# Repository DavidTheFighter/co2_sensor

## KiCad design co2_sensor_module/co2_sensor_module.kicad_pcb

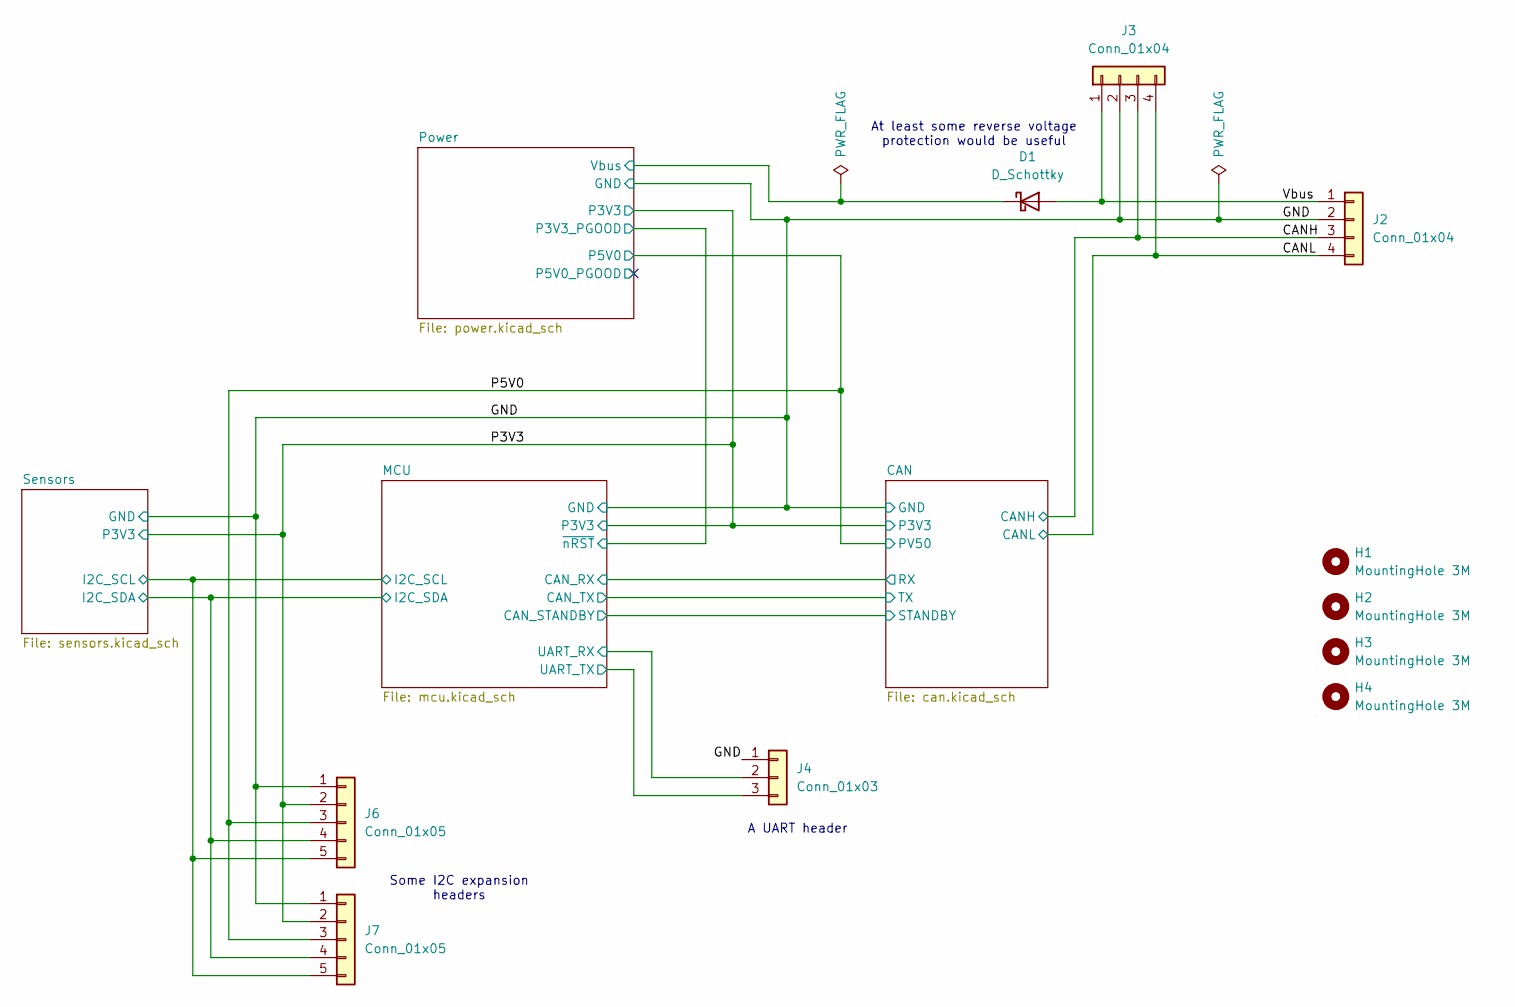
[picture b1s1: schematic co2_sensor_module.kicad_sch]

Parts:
D1: D_Schottky; D_SOD-123; LCSC C8598
H1, H2, H3, H4: MountingHole 3M; MountingHole_3.2mm_M3
J2, J3: Conn_01x04; JST_PH_B4B-PH-K_1x04_P2.00mm_Vertical
J4: Conn_01x03; PinHeader_1x03_P2.54mm_Vertical
J6, J7: Conn_01x05; PinHeader_1x05_P2.54mm_Vertical

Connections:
/CANH: J2.3, J3.3; also elsewhere on the board
/CANL: J2.4, J3.4; also elsewhere on the board
/GND: J2.2, J3.2, J4.1, J6.1, J7.1; also elsewhere on the board
/MCU/I2C_SCL: J6.5, J7.5; also elsewhere on the board
/MCU/I2C_SDA: J6.4, J7.4; also elsewhere on the board
/MCU/UART_RX: J4.2; also elsewhere on the board
/MCU/UART_TX: J4.3; also elsewhere on the board
/P3V3: J6.2, J7.2; also elsewhere on the board
/P5V0: J6.3, J7.3; also elsewhere on the board
/Power/Vbus: D1.1 (K); also elsewhere on the board
/Vbus: D1.2 (A), J2.1, J3.1

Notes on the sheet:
Some I2C expansion headers
At least some reverse voltage protection would be useful
A UART header

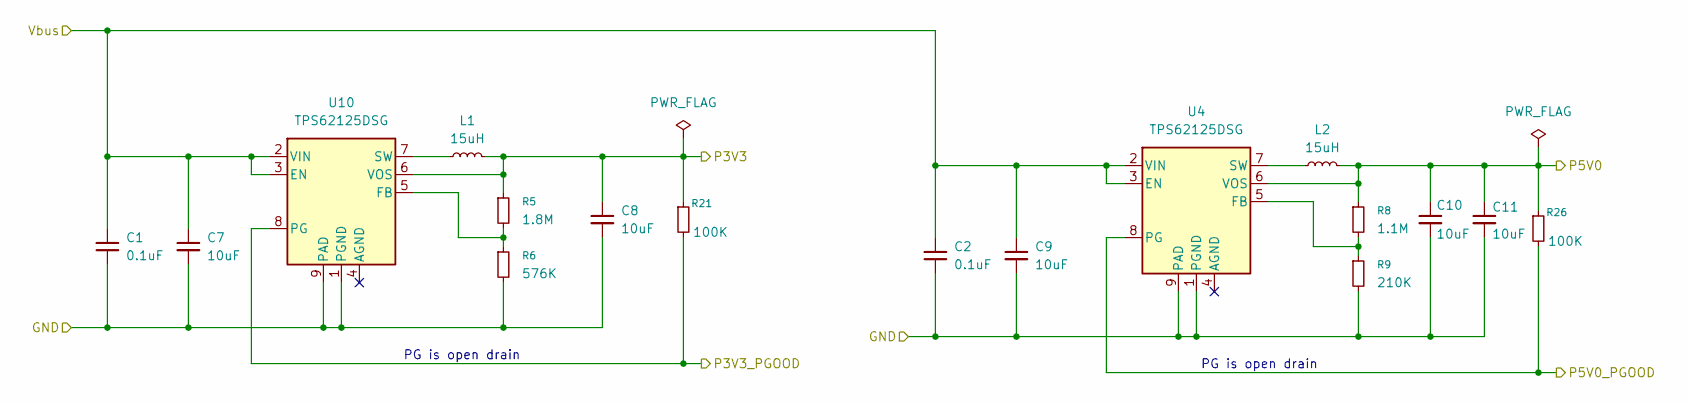
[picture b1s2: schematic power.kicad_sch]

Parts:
C1, C2: 0.1uF; C_0603_1608Metric; LCSC C14663
C7, C8, C9, C10, C11: 10uF; C_0805_2012Metric; LCSC C15850
L1, L2: 15uH; L_1008_2520Metric; LCSC C5832376
R5: 1.8M; R_0402_1005Metric; LCSC C2933079
R6: 576K; R_0402_1005Metric; LCSC C2085028
R8: 1.1M; R_0402_1005Metric; LCSC C2930013
R9: 210K; R_0402_1005Metric; LCSC C2998176
R21, R26: 100K; C_0402_1005Metric; LCSC C25741
U4, U10: TPS62125DSG; Texas_DSG0008A_WSON-8-1EP_2x2mm_P0.5mm_EP0.9x1.6mm; LCSC C324076

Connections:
/GND: C1.2, C2.2, C7.2, C8.2, C9.2, C10.2, C11.2, R6.2, R9.2, U4.1 (PGND), U4.9 (PAD), U10.1 (PGND), U10.9 (PAD); also elsewhere on the board
/MCU/~nRST: R21.2, U10.8 (PG); also elsewhere on the board
/P3V3: C8.1, L1.2, R5.1, R21.1, U10.6 (VOS); also elsewhere on the board
/P5V0: C10.1, C11.1, L2.2, R8.1, R26.1, U4.6 (VOS); also elsewhere on the board
/Power/P5V0_PGOOD: R26.2, U4.8 (PG)
/Power/Vbus: C1.1, C2.1, C7.1, C9.1, U4.2 (VIN), U4.3 (EN), U10.2 (VIN), U10.3 (EN); also elsewhere on the board
unnamed: R8.2, R9.1, U4.5 (FB)
unnamed: L2.1, U4.7 (SW)
unnamed: R5.2, R6.1, U10.5 (FB)
unnamed: L1.1, U10.7 (SW)

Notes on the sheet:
PG is open drain

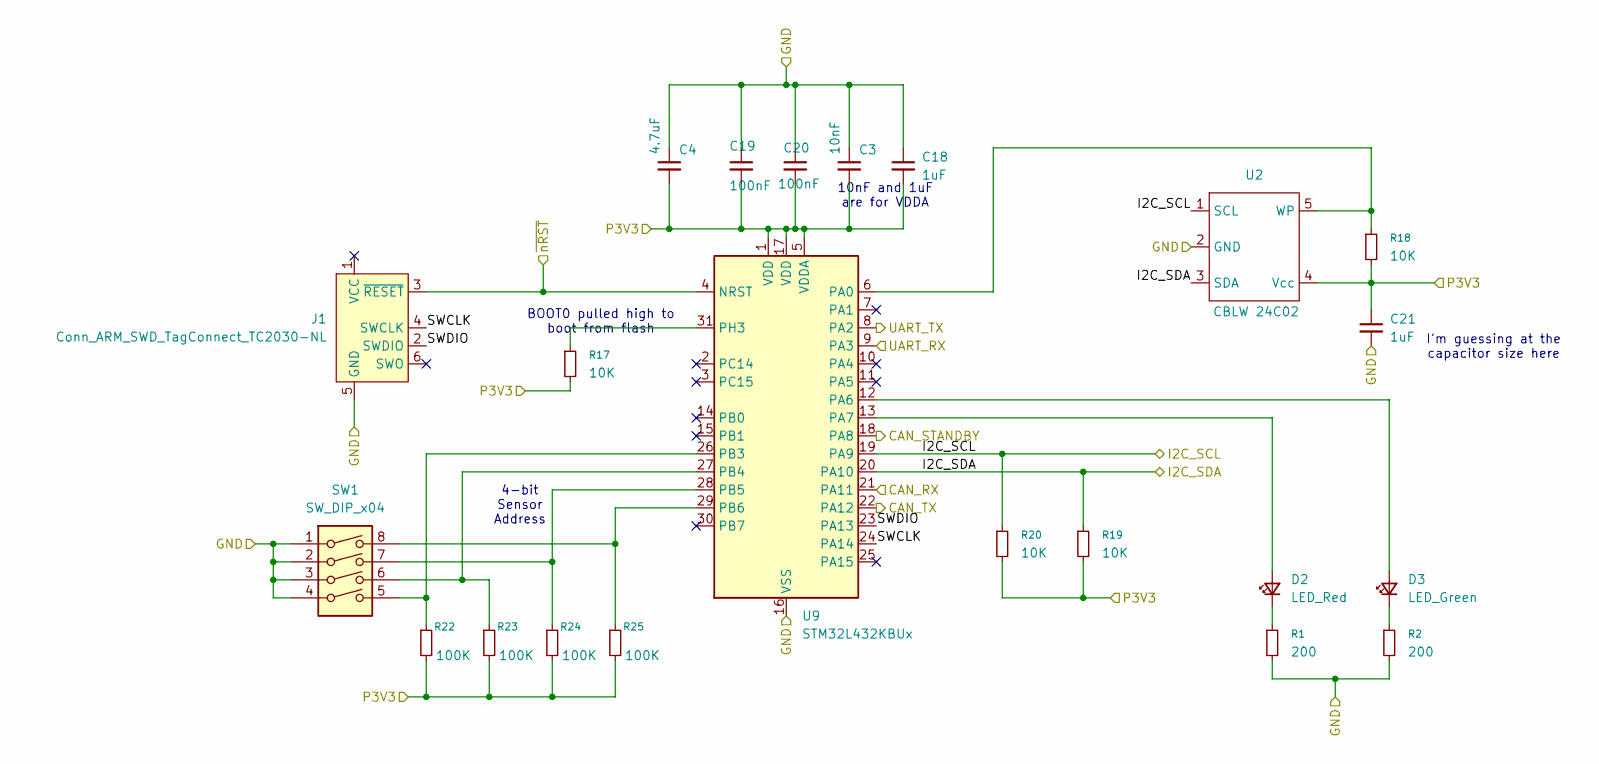
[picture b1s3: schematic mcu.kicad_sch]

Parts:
C3: 10nF; C_0402_1005Metric; LCSC C15195
C4: 4.7uF; C_0603_1608Metric; LCSC C19666
C18, C21: 1uF; C_0603_1608Metric; LCSC C15849
C19, C20: 100nF; C_0402_1005Metric; LCSC C1525
D2: LED_Red; LED_0805_2012Metric; LCSC C84256
D3: LED_Green; LED_0805_2012Metric; LCSC C2297
J1: Conn_ARM_SWD_TagConnect_TC2030-NL; Tag-Connect_TC2030-IDC-NL_2x03_P1.27mm_Vertical
R1, R2: 200; R_0603_1608Metric; LCSC C8218
R17, R18, R19, R20: 10K; R_0402_1005Metric; LCSC C25744
R22, R23, R24, R25: 100K; C_0402_1005Metric; LCSC C25741
SW1: SW_DIP_x04; SW_DIP_SPSTx04_Slide_9.78x12.34mm_W7.62mm_P2.54mm
U2: CBLW 24C02; SOT-23-5; LCSC C18723540
U9: STM32L432KBUx; QFN-32-1EP_5x5mm_P0.5mm_EP3.45x3.45mm; LCSC C2928224

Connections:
/CAN/RX: U9.21 (PA11); also elsewhere on the board
/CAN/STANDBY: U9.18 (PA8); also elsewhere on the board
/CAN/TX: U9.22 (PA12); also elsewhere on the board
/GND: C3.1, C4.1, C18.1, C19.1, C20.1, C21.2, J1.5 (GND), R1.2, R2.2, SW1.1, SW1.2, SW1.3, SW1.4, U2.2 (GND), U9.16 (VSS), U9.32 (VSS), U9.33 (VSS); also elsewhere on the board
/MCU/I2C_SCL: R20.1, U2.1 (SCL), U9.19 (PA9); also elsewhere on the board
/MCU/I2C_SDA: R19.1, U2.3 (SDA), U9.20 (PA10); also elsewhere on the board
/MCU/SWCLK: J1.4 (SWCLK), U9.24 (PA14)
/MCU/SWDIO: J1.2 (SWDIO), U9.23 (PA13)
/MCU/UART_RX: U9.9 (PA3); also elsewhere on the board
/MCU/UART_TX: U9.8 (PA2); also elsewhere on the board
/MCU/~nRST: J1.3 (~RESET), U9.4 (NRST); also elsewhere on the board
/P3V3: C3.2, C4.2, C18.2, C19.2, C20.2, C21.1, R17.2, R18.2, R19.2, R20.2, R22.2, R23.2, R24.2, R25.2, U2.4 (Vcc), U9.1 (VDD), U9.5 (VDDA), U9.17 (VDD); also elsewhere on the board
unnamed: D2.2 (A), U9.13 (PA7)
unnamed: D2.1 (K), R1.1
unnamed: D3.2 (A), U9.12 (PA6)
unnamed: D3.1 (K), R2.1
unnamed: R18.1, U2.5 (WP), U9.6 (PA0)
unnamed: R22.1, SW1.5, U9.26 (PB3)
unnamed: R23.1, SW1.6, U9.27 (PB4)
unnamed: R24.1, SW1.7, U9.28 (PB5)
unnamed: R25.1, SW1.8, U9.29 (PB6)
unnamed: R17.1, U9.31 (PH3)

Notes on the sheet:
BOOT0 pulled high to boot from flash
I'm guessing at the capacitor size here
10nF and 1uF are for VDDA
4-bit Sensor Address

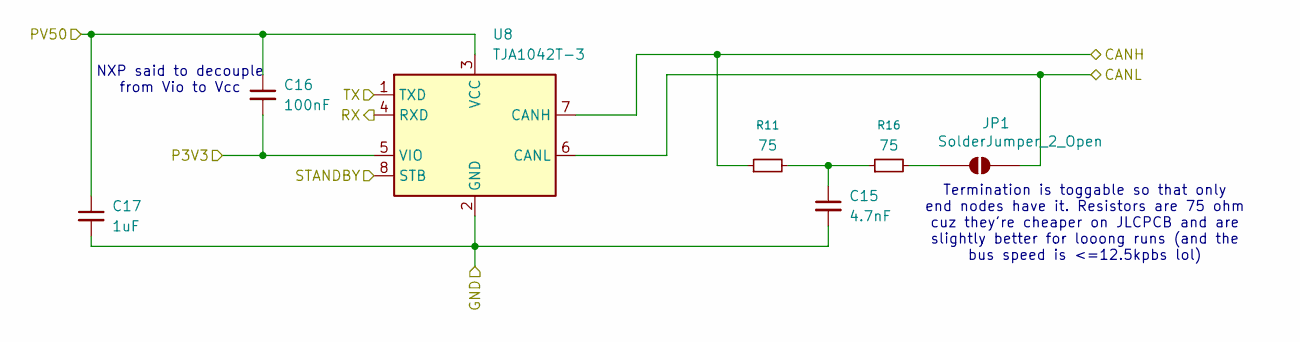
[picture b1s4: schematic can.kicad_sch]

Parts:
C15: 4.7nF; C_0805_2012Metric; LCSC C1744
C16: 100nF; C_0402_1005Metric; LCSC C1525
C17: 1uF; C_0603_1608Metric; LCSC C15849
JP1: SolderJumper_2_Open; SolderJumper-2_P1.3mm_Open_TrianglePad1.0x1.5mm
R11, R16: 75; R_0603_1608Metric; LCSC C4275
U8: TJA1042T-3; SOIC-8_3.9x4.9mm_P1.27mm; LCSC C132227

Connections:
/CAN/RX: U8.4 (RXD); also elsewhere on the board
/CAN/STANDBY: U8.8 (STB); also elsewhere on the board
/CAN/TX: U8.1 (TXD); also elsewhere on the board
/CANH: R11.1, U8.7 (CANH); also elsewhere on the board
/CANL: JP1.2 (B), U8.6 (CANL); also elsewhere on the board
/GND: C15.2, C17.2, U8.2 (GND); also elsewhere on the board
/P3V3: C16.2, U8.5 (VIO); also elsewhere on the board
/P5V0: C16.1, C17.1, U8.3 (VCC); also elsewhere on the board
unnamed: C15.1, R11.2, R16.1
unnamed: JP1.1 (A), R16.2

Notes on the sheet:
Termination is toggable so that only end nodes have it. Resistors are 75 ohm cuz they're cheaper on JLCPCB and are slightly better for looong runs (and the bus speed is <=12.5kpbs lol)
NXP said to decouple from Vio to Vcc

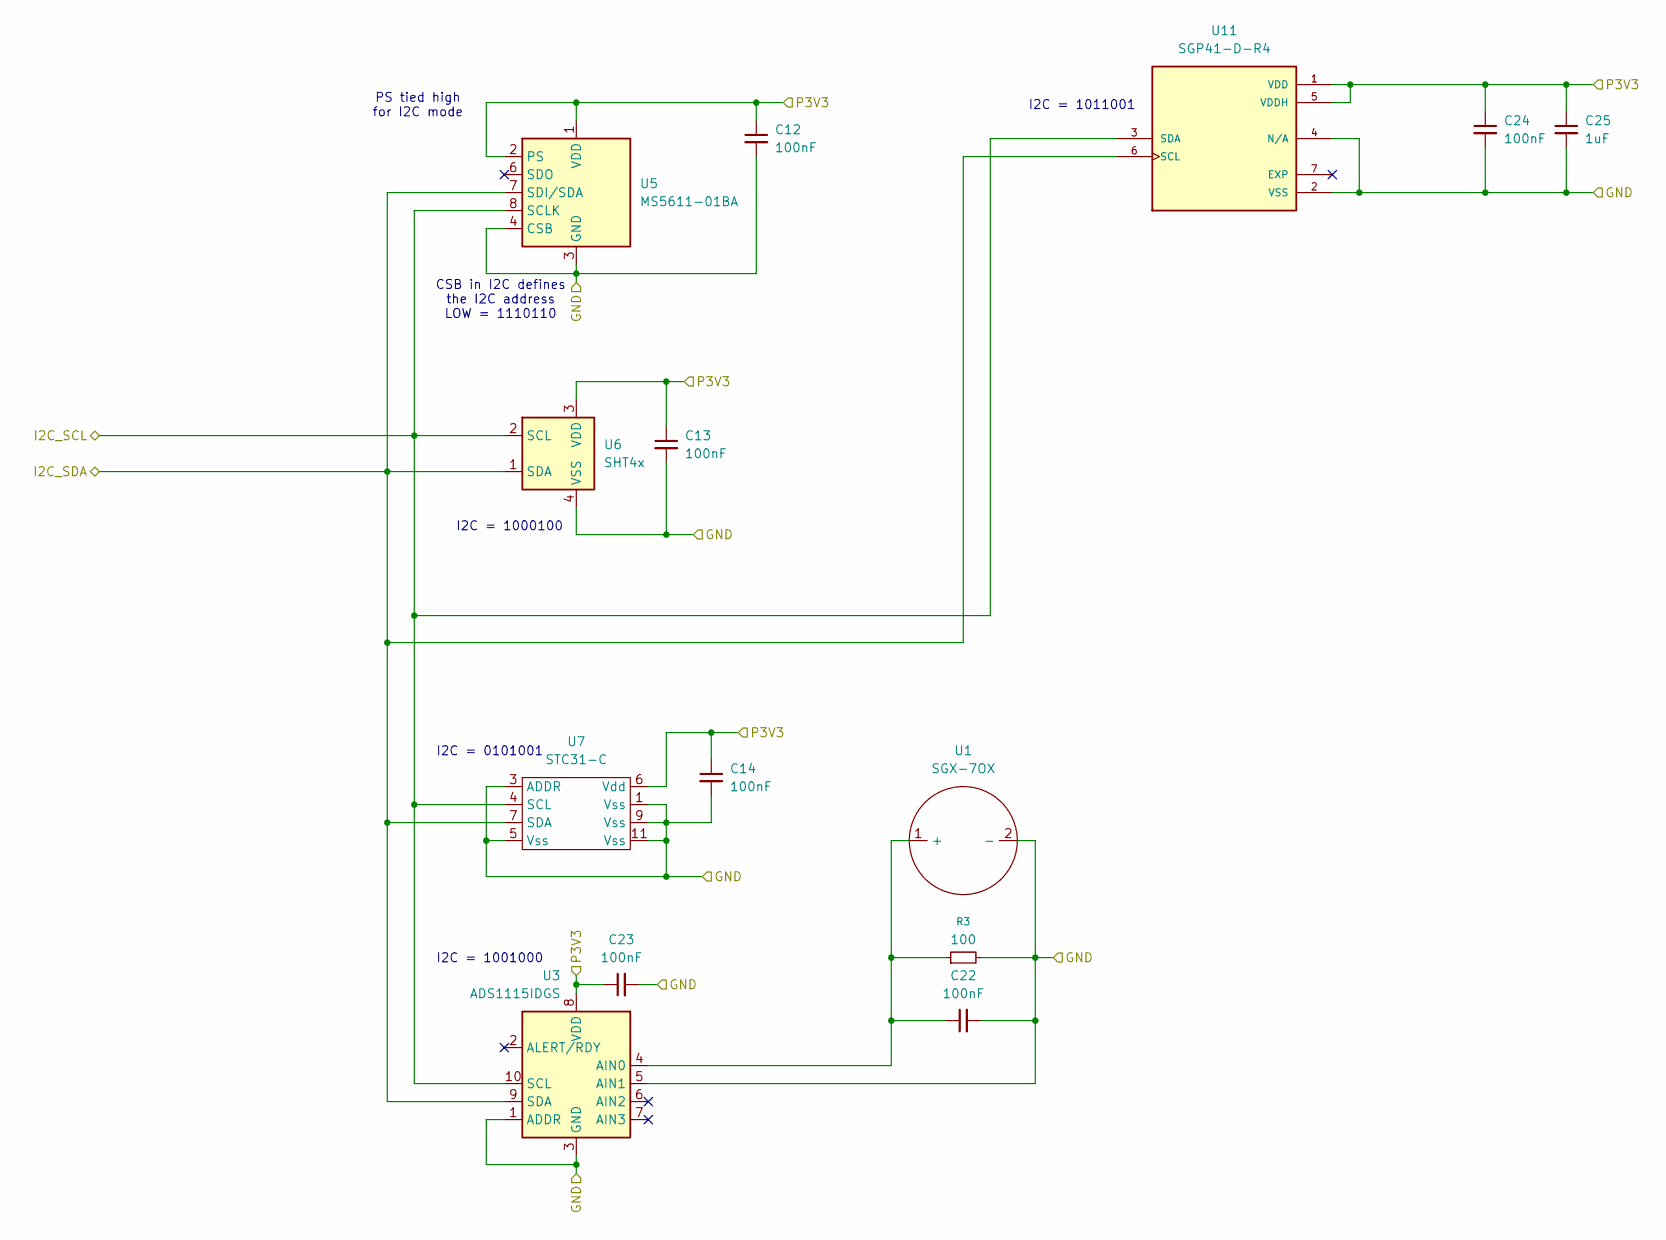
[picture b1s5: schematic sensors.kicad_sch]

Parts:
C12, C13, C14, C22, C23, C24: 100nF; C_0402_1005Metric; LCSC C1525
C25: 1uF; C_0603_1608Metric; LCSC C15849
R3: 100; R_0603_1608Metric; LCSC C122970
U1: SGX-7OX
U3: ADS1115IDGS; TSSOP-10_3x3mm_P0.5mm; LCSC C37593
U5: MS5611-01BA; LGA-8_3x5mm_P1.25mm; LCSC C15639
U6: SHT4x; Sensirion_DFN-4_1.5x1.5mm_P0.8mm_SHT4x_NoCentralPad; LCSC C2909890
U7: STC31-C; STC31-C-R5; LCSC C22396918
U11: SGP41-D-R4; XDCR_SGP41-D-R4; LCSC C3659325

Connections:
/GND: C12.2, C13.2, C14.2, C22.2, C23.2, C24.2, C25.2, R3.2, U1.2 (-), U3.1 (ADDR), U3.3 (GND), U3.5 (AIN1), U5.3 (GND), U5.4 (CSB), U5.5 (CSB), U6.4 (VSS), U7.1 (Vss), U7.3 (ADDR), U7.5 (Vss), U7.9 (Vss), U7.11 (Vss), U11.2 (VSS), U11.4 (N/A); also elsewhere on the board
/MCU/I2C_SCL: U3.10 (SCL), U5.8 (SCLK), U6.2 (SCL), U7.4 (SCL), U11.3 (SDA); also elsewhere on the board
/MCU/I2C_SDA: U3.9 (SDA), U5.7 (SDI/SDA), U6.1 (SDA), U7.7 (SDA), U11.6 (SCL); also elsewhere on the board
/P3V3: C12.1, C13.1, C14.1, C23.1, C24.1, C25.1, U3.8 (VDD), U5.1 (VDD), U5.2 (PS), U6.3 (VDD), U7.6 (Vdd), U11.1 (VDD), U11.5 (VDDH); also elsewhere on the board
unnamed: C22.1, R3.1, U1.1 (+), U3.4 (AIN0)

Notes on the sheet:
I2C = 1001000
I2C = 0101001
PS tied high for I2C mode
I2C = 1011001
CSB in I2C defines the I2C address LOW = 1110110
I2C = 1000100

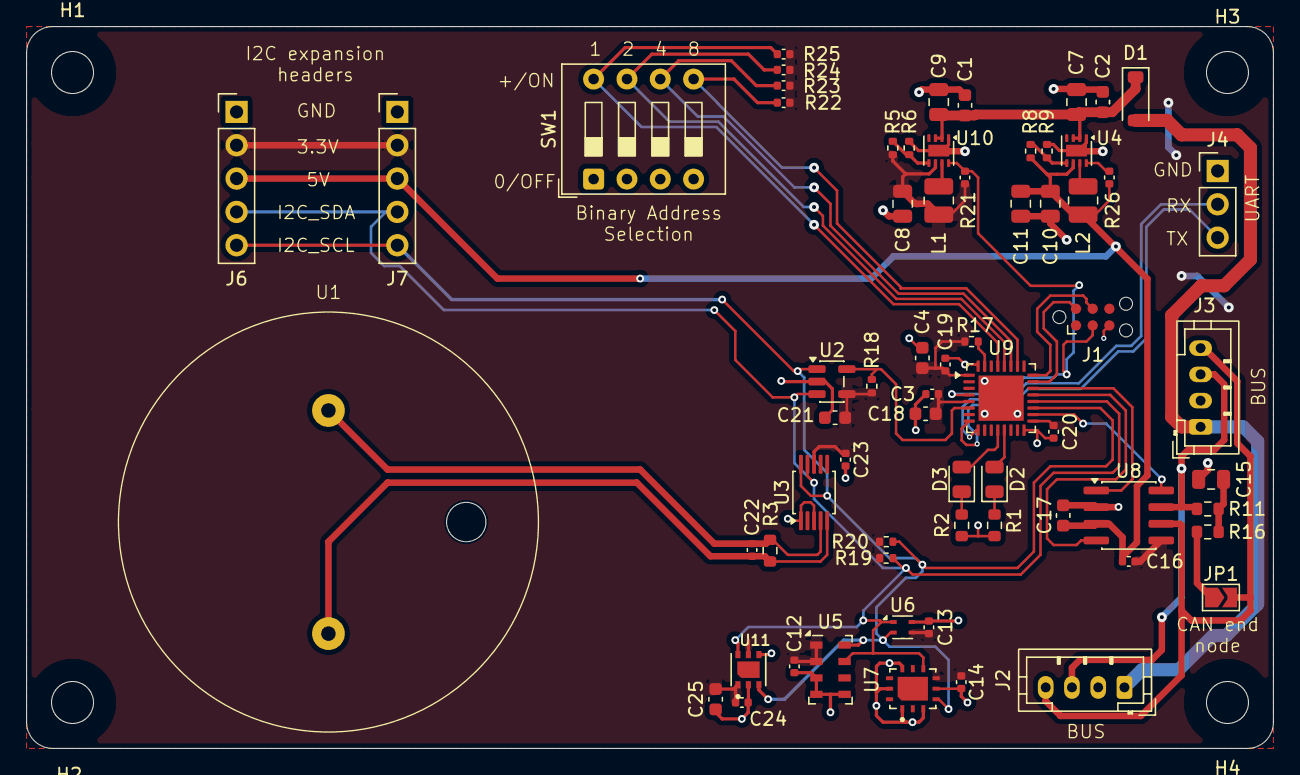
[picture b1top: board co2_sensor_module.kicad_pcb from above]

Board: 2 copper layers, 95.0 x 55.0 mm, 70 parts (0 on the bottom side), 35 nets.

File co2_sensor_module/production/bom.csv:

Designator,Footprint,Quantity,Value,LCSC Part #
"C10, C11, C7, C8, C9",0805,5,10uF,C15850
"C12, C13, C14, C16, C19, C20, C22, C23",0402,8,100nF,C1525
C15,0805,1,4.7nF,C1744
"C17, C18, C21",0603,3,1uF,C15849
C3,0402,1,10nF,C15195
C4,0603,1,4.7uF,C19666
D1,D_SOD-123,1,D_Schottky,C8598
D2,0805,1,LED_Red,C84256
D3,0805,1,LED_Green,C2297
"J2, J3",JST_PH_B4B-PH-K_1x04_P2.00mm_Vertical,2,Conn_01x04,
J4,PinHeader_1x03_P2.54mm_Vertical,1,Conn_01x03,
"J6, J7",PinHeader_1x05_P2.54mm_Vertical,2,Conn_01x05,
"L1, L2",1008,2,15uH,C5832376
"R1, R2",0603,2,200,C8218
"R11, R16",0603,2,75,C4275
"R17, R18, R19, R20",0402,4,10K,C25744
"R21, R22, R23, R24, R25, R26",0402,6,100K,C25741
R3,0603,1,100,C122970
R5,0402,1,1.8M,C2933079
R6,0402,1,576K,C2085028
R8,0402,1,1.1M,C2930013
R9,0402,1,210K,C2998176
SW1,SW_DIP_SPSTx04_Slide_9.78x12.34mm_W7.62mm_P2.54mm,1,SW_DIP_x04,
U1,SGX-7OX,1,SGX-7OX,
"U10, U4",Texas_DSG0008A_WSON-8-1EP_2x2mm_P0.5mm_EP0.9x1.6mm,2,TPS62125DSG,C324076
U2,SOT-23-5,1,CBLW 24C02,C18723540
U3,TSSOP-10_3x3mm_P0.5mm,1,ADS1115IDGS,C37593
U5,LGA-8_3x5mm_P1.25mm,1,MS5611-01BA,C15639
U6,Sensirion_DFN-4_1.5x1.5mm_P0.8mm_SHT4x_NoCentralPad,1,SHT4x,C2909890
U7,STC31-C-R5,1,STC31-C,C22396918
U8,SOIC-8_3.9x4.9mm_P1.27mm,1,TJA1042T-3,C132227
U9,QFN-32-1EP_5x5mm_P0.5mm_EP3.45x3.45mm,1,STM32L432KBUx,C2928224

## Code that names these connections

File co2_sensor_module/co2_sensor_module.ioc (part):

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Mcu.Name=STM32L432K(B-C)Ux
Mcu.Package=UFQFPN32
Mcu.UserName=STM32L432KBUx
PA10.Mode=I2C
PA10.Signal=I2C1_SDA
PA11.Mode=CAN_Activate
PA11.Signal=CAN1_RX
PA12.Mode=CAN_Activate
PA12.Signal=CAN1_TX
PA13\ (JTMS-SWDIO).Mode=Serial_Wire
PA13\ (JTMS-SWDIO).Signal=SYS_JTMS-SWDIO
PA14\ (JTCK-SWCLK).Mode=Serial_Wire
PA14\ (JTCK-SWCLK).Signal=SYS_JTCK-SWCLK
PA2.Mode=Asynchronous
PA2.Signal=LPUART1_TX
PA3.Mode=Asynchronous
PA3.Signal=LPUART1_RX
PA9.Mode=I2C
PA9.Signal=I2C1_SCL
RCC.HSE_VALUE=8000000
board=custom
